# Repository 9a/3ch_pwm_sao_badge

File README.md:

# 3ch_pwm_sao_badge
A sao compatible 3ch PWM mini badge for LEDs/LED noodles using a attiny402

KiCad files for version 7.0

In Arduino IDE: deactivate millis() in the "tools" section

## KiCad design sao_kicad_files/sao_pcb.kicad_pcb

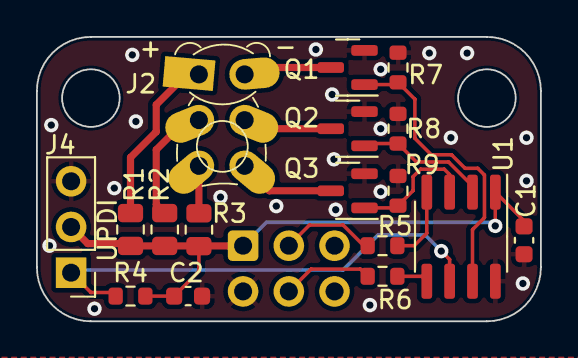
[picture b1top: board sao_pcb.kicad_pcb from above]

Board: 2 copper layers, 28.0 x 15.8 mm, 18 parts (1 on the bottom side), 16 nets.

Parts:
C1: 100n; C_0603_1608Metric
C2: 4.7u; C_0603_1608Metric
J1: Conn_02x03_Odd_Even; IDC-Header_2x03_P2.54mm_Vertical
J2: Conn_02x03_Odd_Even; PinHeader_2x03_P2.54mm_Vertical
J4: Conn_01x03; PinHeader_1x03_P2.54mm_Vertical
Q1, Q2, Q3: 2N7002; SOT-23
R1, R2, R3: 22; R_0805_2012Metric
R4, R7, R8, R9: 10k; R_0603_1608Metric
R5, R6: 0R; R_0603_1608Metric
U1: ATtiny402-SS; SOIC-8_3.9x4.9mm_P1.27mm

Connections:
/3V3: C1.1, C2.1, J1.1, J4.2, R1.1, R2.1, R3.1, R4.2, U1.1 (VCC)
/SCL: J1.4, R6.1
/SDA: J1.3, R5.1
/UPDI: J4.1, R4.1, U1.6 (~RESET/PA0)
GND: C1.2, C2.2, J1.2, J4.3, Q1.2 (S), Q2.2 (S), Q3.2 (S), R7.1, R8.1, R9.1, U1.8 (GND)
unnamed: J2.1, R1.2
unnamed: J2.2, Q1.3 (D)
unnamed: J2.3, R2.2
unnamed: J2.4, Q2.3 (D)
unnamed: J2.5, R3.2
unnamed: J2.6, Q3.3 (D)
unnamed: Q1.1 (G), R7.2, U1.7 (PA3)
unnamed: Q2.1 (G), R8.2, U1.2 (PA6)
unnamed: Q3.1 (G), R9.2, U1.3 (PA7)
unnamed: R5.2, U1.4 (PA1)
unnamed: R6.2, U1.5 (PA2)

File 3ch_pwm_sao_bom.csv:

Reference,Value,Footprint
C1,100n,Capacitor_SMD:C_0603_1608Metric
C2,4.7u,Capacitor_SMD:C_0603_1608Metric
J1,Conn_02x03_Odd_Even,Connector_IDC:IDC-Header_2x03_P2.54mm_Vertical
J2,Conn_02x03_Odd_Even,Connector_PinHeader_2.54mm:PinHeader_2x03_P2.54mm_Vertical
J4,Conn_01x03,Connector_PinHeader_2.54mm:PinHeader_1x03_P2.54mm_Vertical
Q1-Q3,2N7002,Package_TO_SOT_SMD:SOT-23
R1-R3,22,Resistor_SMD:R_0805_2012Metric
"R4, R7-R9",10k,Resistor_SMD:R_0603_1608Metric
"R5, R6",0R,Resistor_SMD:R_0603_1608Metric
U1,ATtiny402-SS,Package_SO:SOIC-8_3.9x4.9mm_P1.27mm

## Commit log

2025-05-21 Update 3ch_pwm_sao_bom.csv
    added 'R'
2025-05-21 Update README.md
    added images
